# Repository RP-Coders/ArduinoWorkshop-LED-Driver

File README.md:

# ArduinoWorkshop-LED-Driver
Course 1 - LED Driver

This project is originally used for a course.

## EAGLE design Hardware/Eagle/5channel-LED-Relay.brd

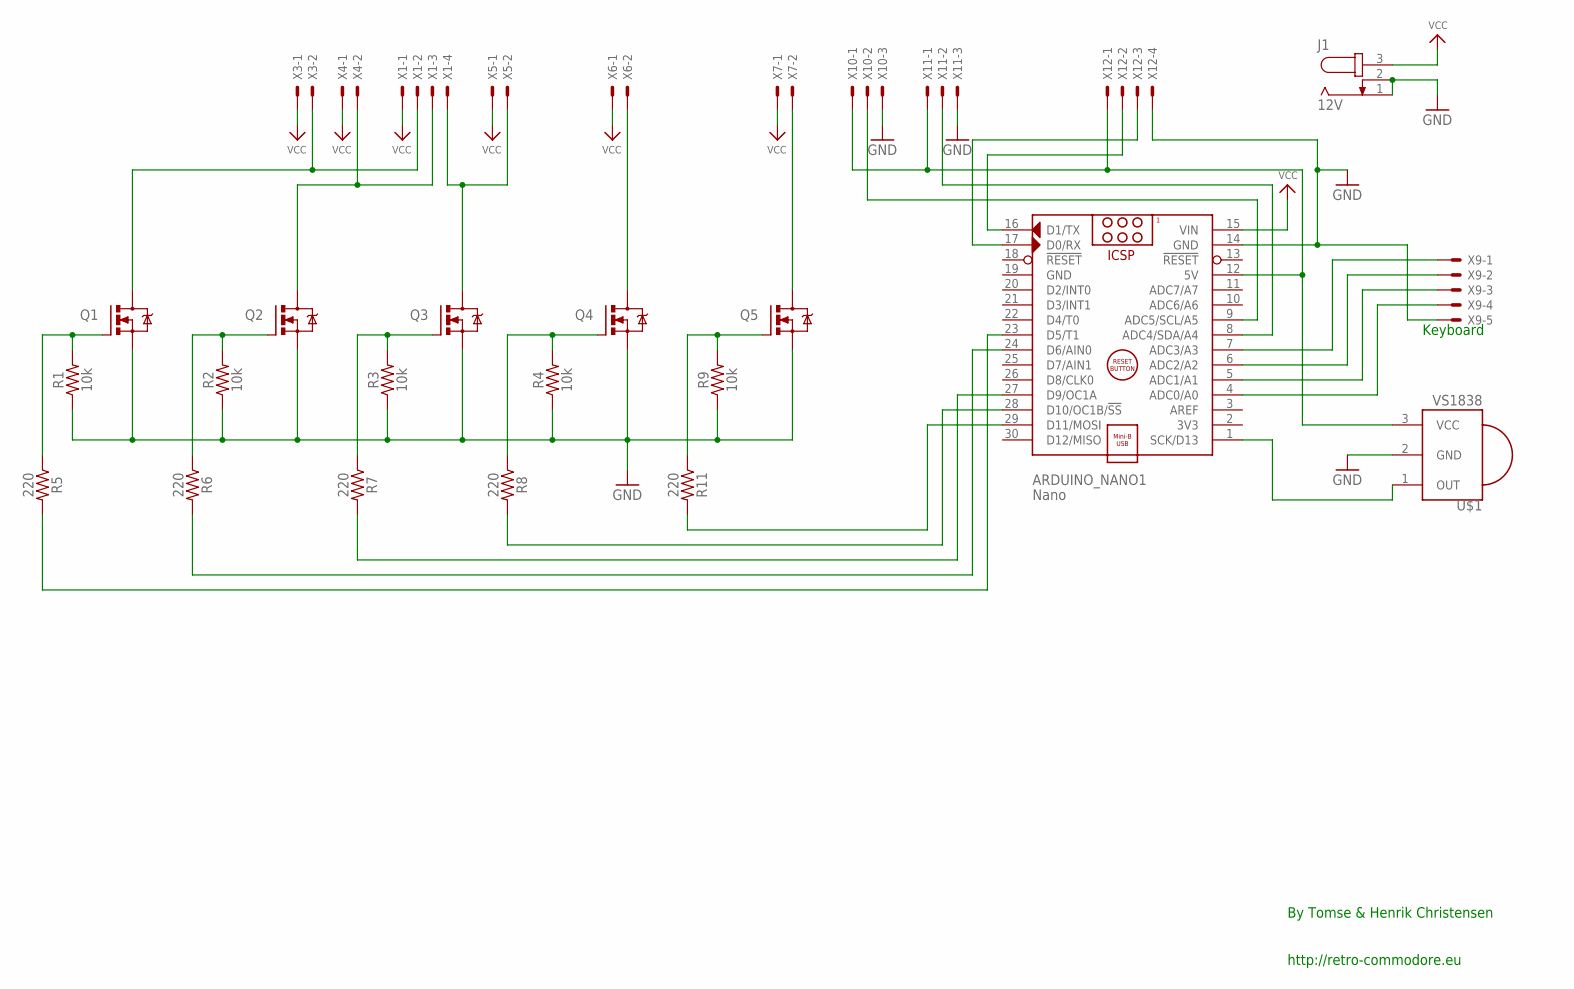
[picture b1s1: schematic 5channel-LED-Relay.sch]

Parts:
ARDUINO_NANO1: Nano; ARDUINO_NANO
J1: 12V; SPC4077
Q1, Q2, Q3, Q4, Q5: FQP30N06L; TO220BV
R1, R2, R3, R4, R9: 10k; AXIAL-0.3
R5, R6, R7, R8, R11: 220; AXIAL-0.3
U$1: VS1838; PNA460XM
X1, X12: JST-XH-04-PIN-LONG-PAD; JST-XH-04-PACKAGE-LONG-PAD
X3, X4, X5, X6, X7: JST-XH-02-PIN-LONG-PAD; JST-XH-02-PACKAGE-LONG-PAD
X9: JST-XH-05-PIN-LONG-PAD; JST-XH-05-PACKAGE-LONG-PAD
X10, X11: JST-XH-03-PIN-LONG-PAD; JST-XH-03-PACKAGE-LONG-PAD

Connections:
5V: ARDUINO_NANO1.12 (5V), U$1.3 (VCC), X10.1, X11.1, X12.1
C01: Q1.D, X1.2, X3.2
C02: Q2.D, X1.3, X4.2
C03: Q3.D, X1.4, X5.2
C04: Q4.D, X6.2
C05: Q5.D, X7.2
GND: ARDUINO_NANO1.14 (GND), ARDUINO_NANO1.19 (GND), J1.1, J1.2, Q1.S, Q2.S, Q3.S, Q4.S, Q5.S, R1.P$1 (1), R2.P$1 (1), R3.P$1 (1), R4.P$1 (1), R9.P$1 (1), U$1.2 (GND), X9.5, X10.3, X11.3, X12.4
unnamed: ARDUINO_NANO1.8 (ADC4/SDA/A4), X11.2
unnamed: ARDUINO_NANO1.9 (ADC5/SCL/A5), X10.2
unnamed: ARDUINO_NANO1.29 (D11/MOSI), R11.P$2 (2)
unnamed: ARDUINO_NANO1.1 (SCK/D13), U$1.1 (OUT)
unnamed: Q4.G, R4.P$2 (2), R8.P$1 (1)
unnamed: ARDUINO_NANO1.23 (D5/T1), R5.P$2 (2)
unnamed: ARDUINO_NANO1.24 (D6/AIN0), R6.P$2 (2)
unnamed: ARDUINO_NANO1.27 (D9/OC1A), R7.P$2 (2)
unnamed: ARDUINO_NANO1.28 (D10/OC1B/!SS), R8.P$2 (2)
unnamed: ARDUINO_NANO1.16 (D1/TX), X12.2
unnamed: Q2.G, R2.P$2 (2), R6.P$1 (1)
unnamed: ARDUINO_NANO1.17 (D0/RX), X12.3
unnamed: ARDUINO_NANO1.7 (ADC3/A3), X9.1
unnamed: Q5.G, R9.P$2 (2), R11.P$1 (1)
unnamed: ARDUINO_NANO1.6 (ADC2/A2), X9.2
unnamed: Q3.G, R3.P$2 (2), R7.P$1 (1)
unnamed: ARDUINO_NANO1.5 (ADC1/A1), X9.3
unnamed: ARDUINO_NANO1.4 (ADC0/A0), X9.4
unnamed: Q1.G, R1.P$2 (2), R5.P$1 (1)
VCC: ARDUINO_NANO1.15 (VIN), J1.3, X1.1, X3.1, X4.1, X5.1, X6.1, X7.1

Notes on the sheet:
Keyboard
By Tomse & Henrik Christensen http://retro-commodore.eu

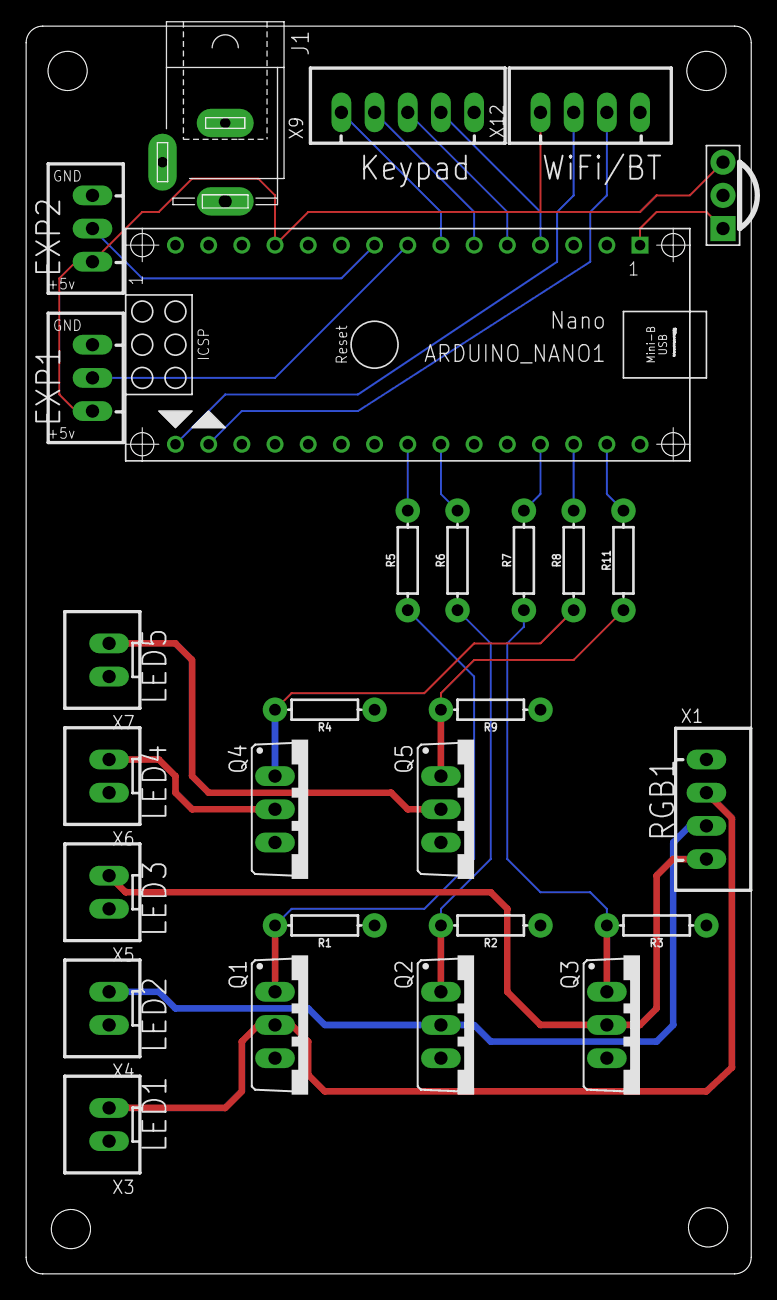
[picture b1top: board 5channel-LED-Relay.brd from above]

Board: 2 copper layers, 55.5 x 95.5 mm, 28 parts (0 on the bottom side), 27 nets.

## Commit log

2018-10-08 Update .gitignore
    Initial commit - Ready for production/course
2018-10-08 Update Code/Arduino workshop/Workshop1/Workshop1.ino
    Added Course Code 1
2018-10-08 Update Code/Arduino workshop/Workshop2/Workshop2.ino
    Added Course Code 2
2018-10-08 Update Code/Arduino workshop/Workshop3/Workshop3.ino
    Added Course Code 3
2018-10-08 Update Doc/LED Driver Workshop.pdf
    Added Release Doc in pdf
2018-10-08 Update Doc/LED Driver Workshop.odt
    Added Release Doc in odt
2018-10-08 Update Hardware/Eagle/5channel-LED-Relay.brd
    Added eagle board
2018-10-08 Update Hardware/Eagle/5channel-LED-Relay.sch
    added eagle schematic
2018-10-08 Update Hardware/Eagle/5channel-LED-Relay_2018-07-18_cam_files.zip
    Added CAM files ready to upload to i.e. jlcpcb
2018-10-08 Create README.md
    Added note for the code files
2019-01-22 Working version - can power on/off single lamp

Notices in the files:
Hardware/Eagle/5channel-LED-Relay.brd:
Copyright (C) 2018
parts and their libraries:
SparkFun-Resistors: Licensing: Creative Commons ShareAlike 4.0 International - https://creativecommons.org/licenses/by-sa/4.0
